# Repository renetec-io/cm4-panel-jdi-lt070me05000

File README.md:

Overview
======

This repository contains a PCB design and drivers for Raspberry Pi CM4 Сarrier with Hi-Res MIPI Display project.<br>
For details, see https://hackaday.io/project/176098-raspberry-pi-cm4-arrier-with-hi-res-mipi-display

The display used is JDI LT070ME05000 with Goodix touch input driver IC. The project also uses MCP23008 IO expander to save some GPIO pins.

Raspberry Pi only supports its official 7-inch MIPI DSI display with FKMS(Fake/Firmware KMS) out of the box. 
To make the display work, we need to use full KMS and Linux kernel driver for the panel.

Setup
======

1. Install the latest Raspberry PI OS image, either on SD card (with CM4 Lite) or onto eMMC.
   With Lite version, you can use [SD card instruction](https://www.raspberrypi.org/documentation/installation/installing-images), 
   otherwise use [eMMC instruction](https://www.raspberrypi.org/documentation/hardware/computemodule/cm-emmc-flashing.md).   
   The jumper that enables boot from usb is located near the micro-USB connector on the PCB.
   
1. Mount `boot` partition onto your computer.

1. Enable and connect the serial console.
   1. Add `enable_uart=1` to the config.txt file on `boot` partition.   
   1. Use the serial interface to connect to Raspberry Pi: [elinux.org instruction](https://elinux.org/RPi_Serial_Connection).   
   
1. Enable USB port. <br>
   By default, to conserve power, USB is not enabled on CM4.<br>
   To enable, add `dtoverlay=dwc2,dr_mode=host` to config.txt.
   
1. Boot your Raspberry Pi and connect it to the internet. If you have a module without Wi-Fi, 
   you need a USB Wi-Fi or Ethernet adapter. 
   If Wi-Fi doesn't work, and you are receiving the message like "Could not communicate with wpa_supplicant" from raspi-config 
   when trying to set up wireless network, you may need to add the following
   ```
   allow-hotplug wlan0
   iface wlan0 inet manual
   wpa-conf /etc/wpa_supplicant/wpa_supplicant.conf
   ```
   to /etc/network/interfaces and then reboot.

1. On the Raspberry Pi, 
   1. Install git and dkms: 
   ```
   sudo apt-get update
   sudo apt-get install git dkms
   ```
   2. Clone the repository and install the drivers
   ```
   git clone https://github.com/renetec-io/cm4-panel-jdi-lt070me05000.git
   cd cm4-panel-jdi-lt070me05000
   ./setup.sh
   ```

1. Enable display driver.<br>
   Add the following in the end of /boot/config.txt:
   ```
   dtparam=i2c_vc=on   
   lcd_ignore=1   
   dtoverlay=vc4-kms-v3d-pi4,noaudio   
   dtoverlay=cm4-dsi-lt070me05000   
   ```
   
1. Enable sound.<br>
   Add the following to /boot/config.txt:
   ```
   # Sound configuration   
   dtparam=audio=on   
   dtoverlay=hifiberry-dac   
   dtoverlay=i2s-mmap   
   ```   

8. Reboot.

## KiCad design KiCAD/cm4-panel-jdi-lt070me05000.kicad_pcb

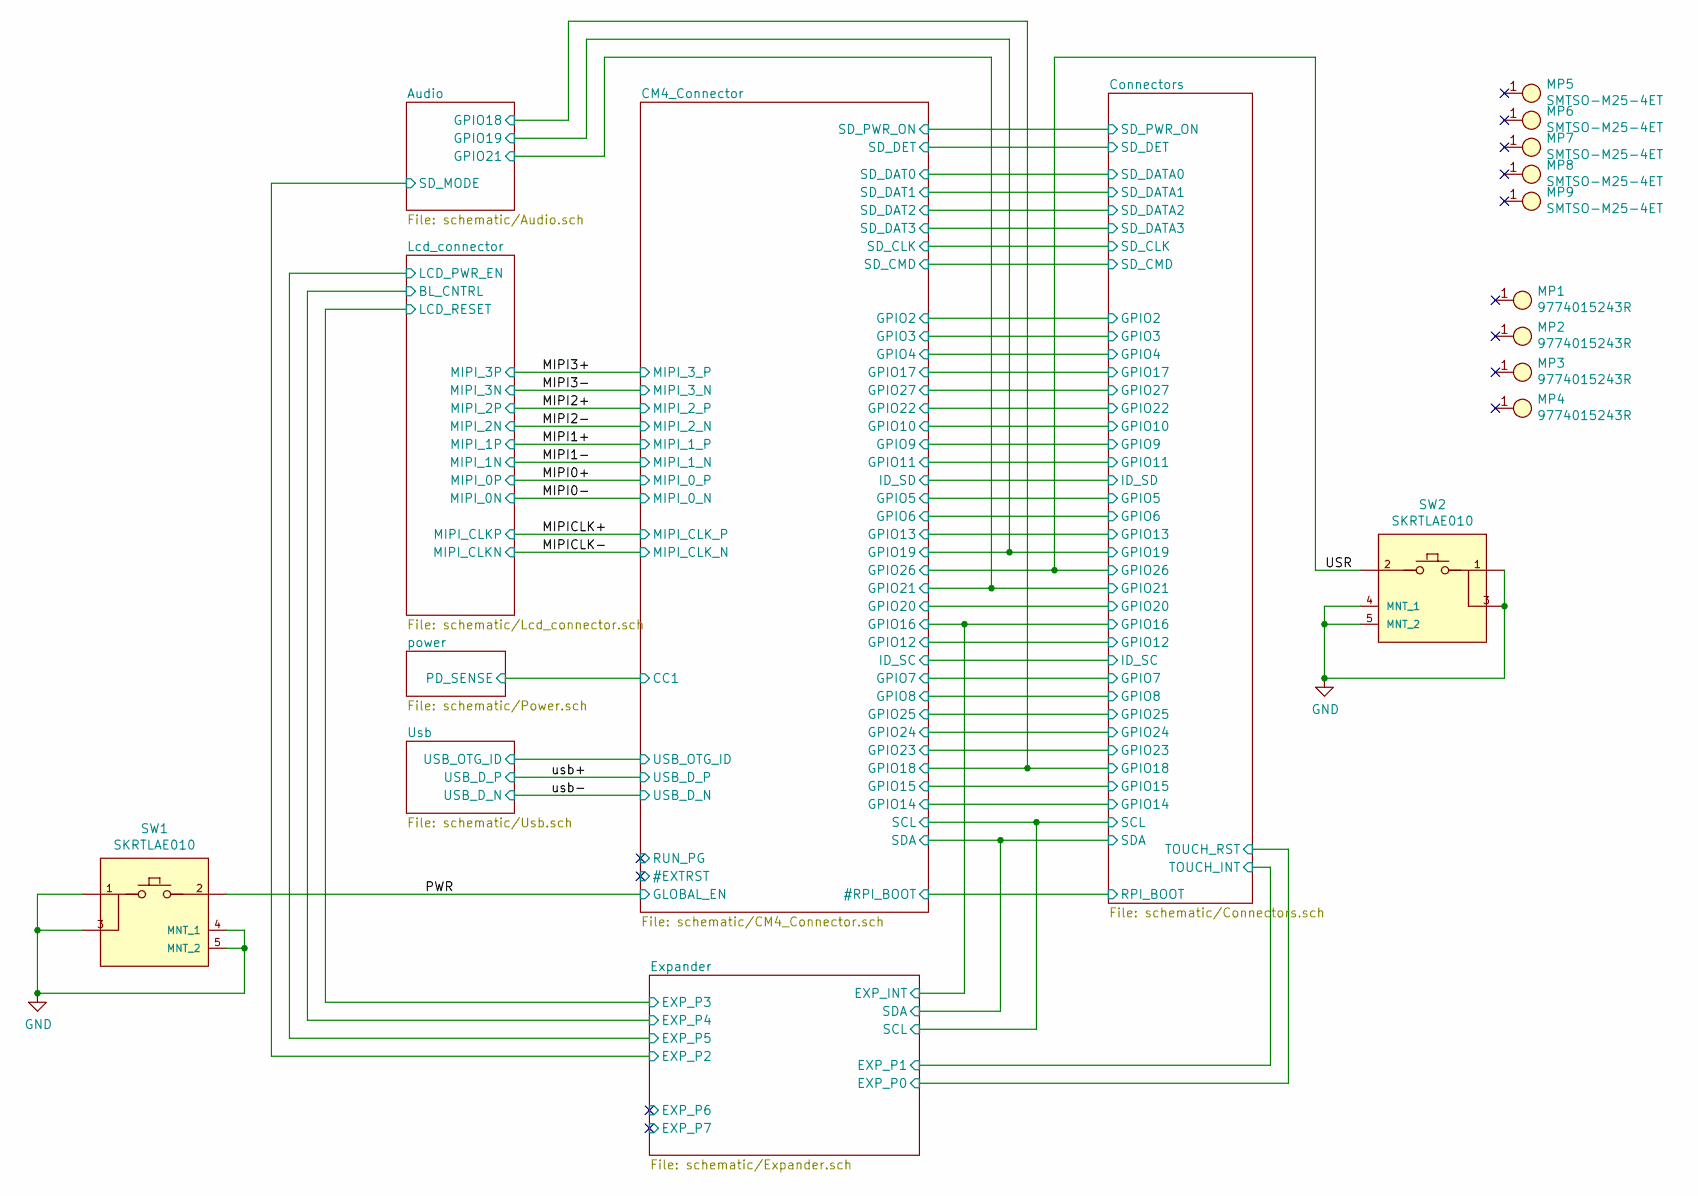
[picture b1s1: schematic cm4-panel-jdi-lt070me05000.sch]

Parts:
MP1, MP2, MP3, MP4: 9774015243R
MP5, MP6, MP7, MP8, MP9: SMTSO-M25-4ET
SW1, SW2: SKRTLAE010; ALPS-SKRTLAE010-0-0-0; voltage rating DC 12V; mouser part number 688-SKRTLA; mouser description Switch Tactile N.O. SPST Round Button J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

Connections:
/PWR: SW1.2; also elsewhere on the board
/USR: SW2.2; also elsewhere on the board
GND: SW1.1, SW1.3, SW1.4 (MNT_1), SW1.5 (MNT_2), SW2.1, SW2.3, SW2.4 (MNT_1), SW2.5 (MNT_2); also elsewhere on the board

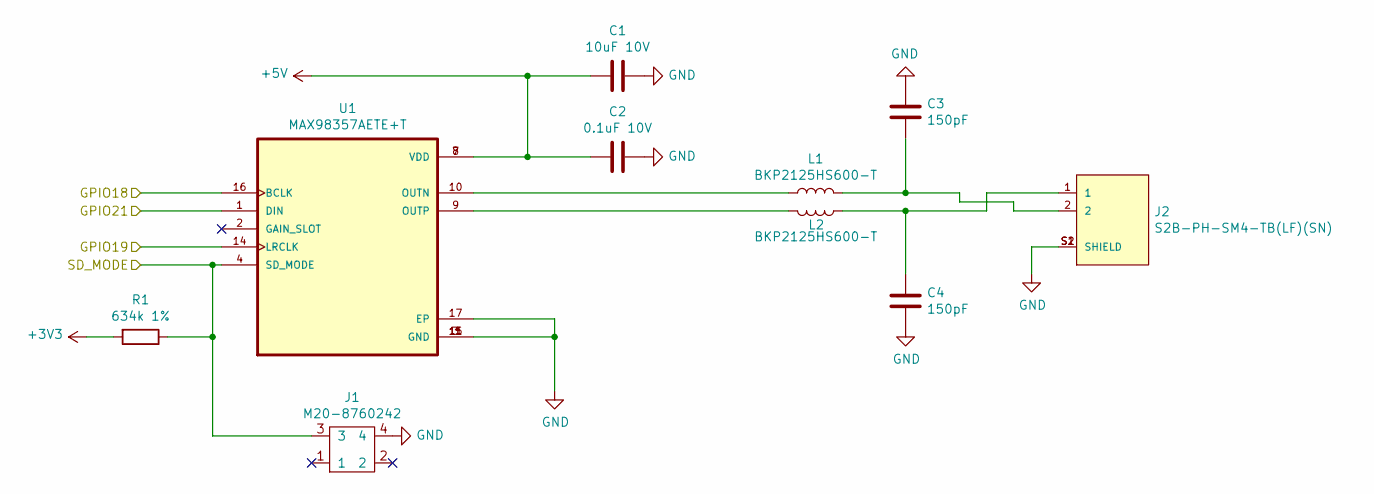
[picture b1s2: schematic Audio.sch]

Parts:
C1: 10uF 10V; C_0603_1608Metric
C2: 0.1uF 10V; C_0603_1608Metric
C3, C4: 150pF; C_0603_1608Metric
J1: M20-8760242
J2: S2B-PH-SM4-TB(LF)(SN); JST_S2B-PH-SM4-TB(LF)(SN)
L1, L2: BKP2125HS600-T; L_0805_2012Metric
R1: 634k 1%; R_0603_1608Metric
U1: MAX98357AETE+T; QFN50P300X300X80-17N

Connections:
+3V3: R1.2; also elsewhere on the board
+5V: C1.2, C2.2, U1.7 (VDD), U1.8 (VDD); also elsewhere on the board
/Audio/GPIO18: U1.16 (BCLK); also elsewhere on the board
/Audio/GPIO19: U1.14 (LRCLK); also elsewhere on the board
/Audio/GPIO21: U1.1 (DIN); also elsewhere on the board
/Expander/EXP_P2: J1.3, R1.1, U1.4 (SD_MODE); also elsewhere on the board
GND: C1.1, C2.1, C3.2, C4.1, J1.4, J2.S1 (SHIELD), J2.S2 (SHIELD), U1.3 (GND), U1.11 (GND), U1.15 (GND), U1.17 (EP); also elsewhere on the board
unnamed: C3.1, J2.2, L1.2
unnamed: C4.2, J2.1, L2.2
unnamed: L1.1, U1.10 (OUTN)
unnamed: L2.1, U1.9 (OUTP)

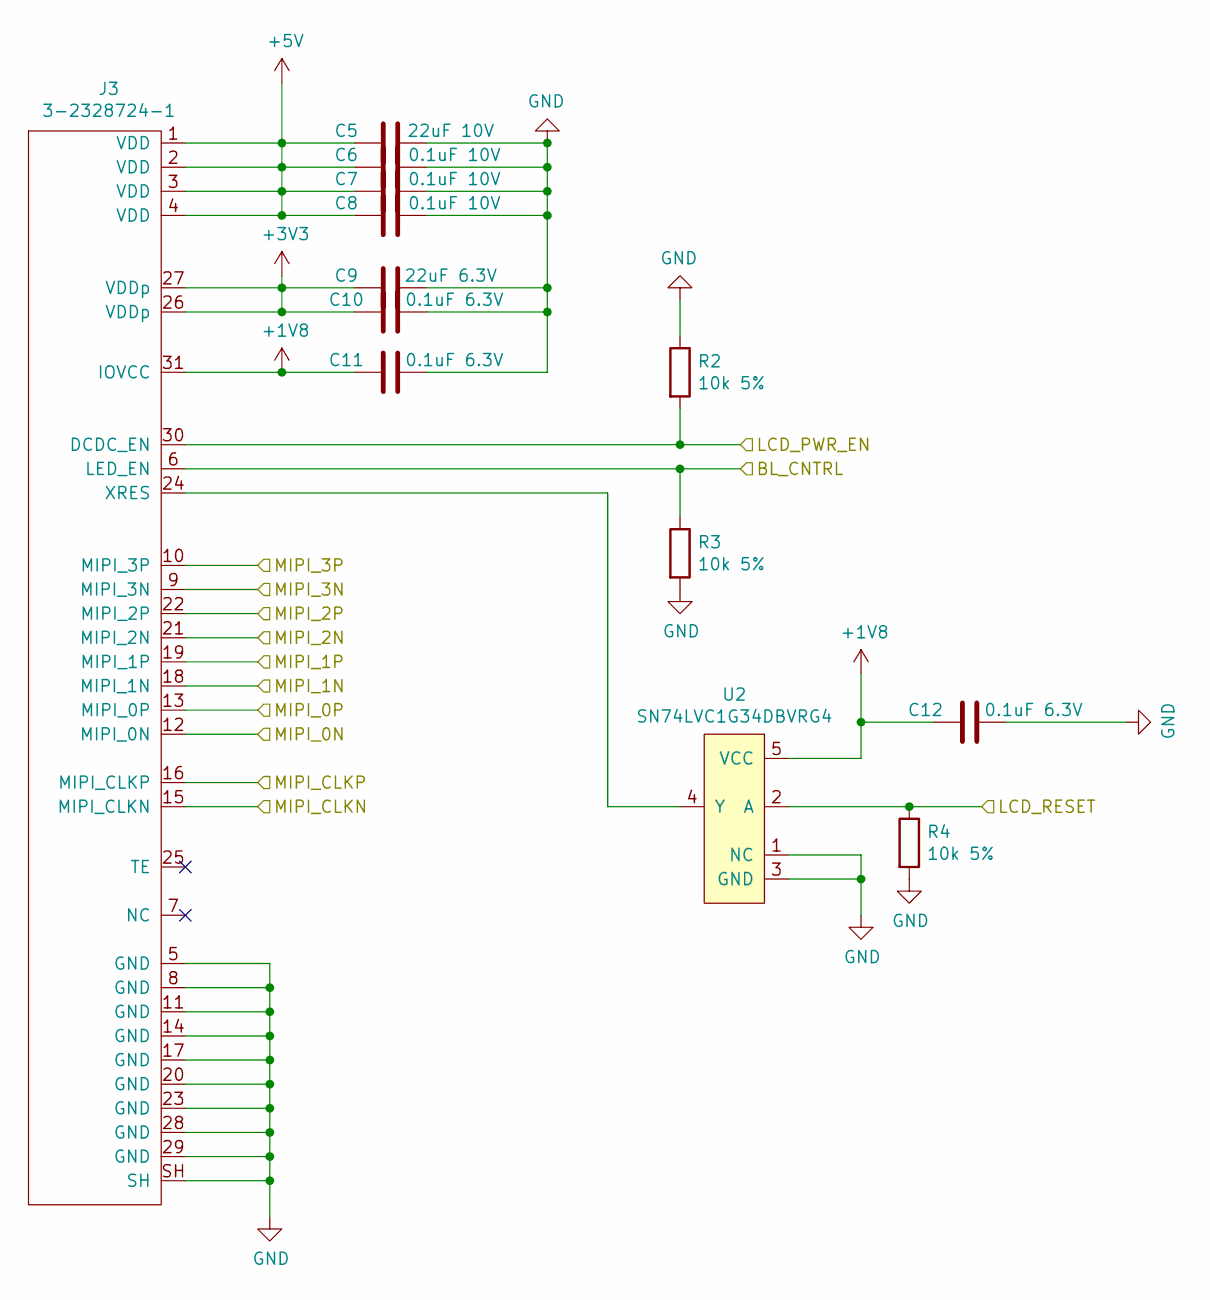
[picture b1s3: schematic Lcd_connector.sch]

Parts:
C5: 22uF 10V; C_0805_2012Metric
C6, C7, C8: 0.1uF 10V; C_0603_1608Metric
C9: 22uF 6.3V; C_0805_2012Metric
C10, C11, C12: 0.1uF 6.3V; C_0603_1608Metric
J3: 3-2328724-1
R2, R3, R4: 10k 5%; R_0603_1608Metric
U2: SN74LVC1G34DBVRG4; SOT95P280X145-5N

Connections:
+1V8: C11.2, C12.2, J3.31 (IOVCC), U2.5 (VCC); also elsewhere on the board
+3V3: C9.2, C10.2, J3.26 (VDDp), J3.27 (VDDp); also elsewhere on the board
+5V: C5.2, C6.2, C7.2, C8.2, J3.1 (VDD), J3.2 (VDD), J3.3 (VDD), J3.4 (VDD); also elsewhere on the board
/Expander/EXP_P3: R4.1, U2.2 (A); also elsewhere on the board
/Expander/EXP_P5: J3.30 (DCDC_EN), R2.2; also elsewhere on the board
/Lcd_connector/BL_CNTRL: J3.6 (LED_EN), R3.1; also elsewhere on the board
/MIPI0+: J3.13 (MIPI_0P); also elsewhere on the board
/MIPI0-: J3.12 (MIPI_0N); also elsewhere on the board
/MIPI1+: J3.19 (MIPI_1P); also elsewhere on the board
/MIPI1-: J3.18 (MIPI_1N); also elsewhere on the board
/MIPI2+: J3.22 (MIPI_2P); also elsewhere on the board
/MIPI2-: J3.21 (MIPI_2N); also elsewhere on the board
/MIPI3+: J3.10 (MIPI_3P); also elsewhere on the board
/MIPI3-: J3.9 (MIPI_3N); also elsewhere on the board
/MIPICLK+: J3.16 (MIPI_CLKP); also elsewhere on the board
/MIPICLK-: J3.15 (MIPI_CLKN); also elsewhere on the board
GND: C5.1, C6.1, C7.1, C8.1, C9.1, C10.1, C11.1, C12.1, J3.5 (GND), J3.8 (GND), J3.11 (GND), J3.14 (GND), J3.17 (GND), J3.20 (GND), J3.23 (GND), J3.28 (GND), J3.29 (GND), J3.SH, R2.1, R3.2, R4.2, U2.1 (NC), U2.3 (GND); also elsewhere on the board
unnamed: J3.24 (XRES), U2.4 (Y)

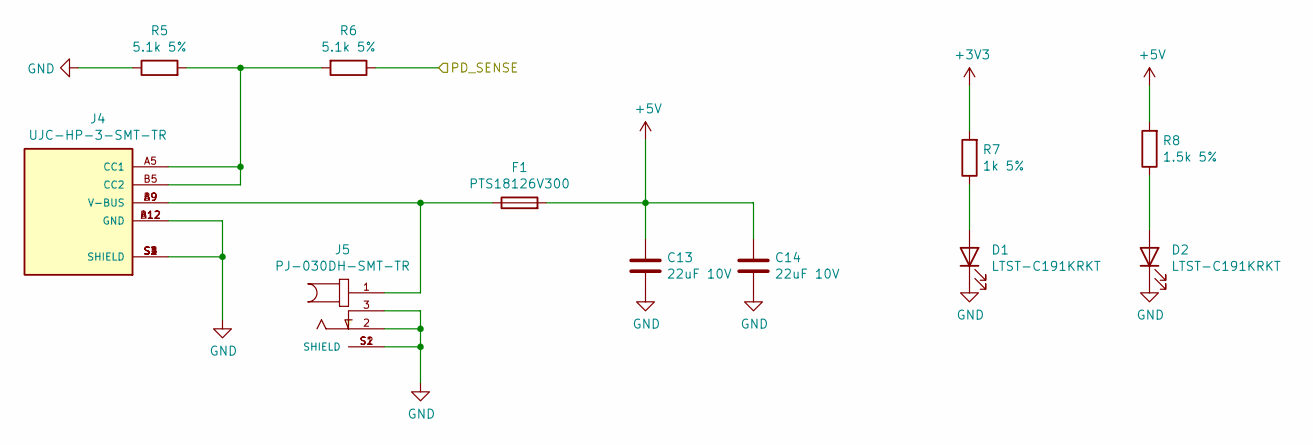
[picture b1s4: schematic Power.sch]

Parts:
C13, C14: 22uF 10V; C_0805_2012Metric
D1, D2: LTST-C191KRKT; LED_0603_1608Metric
F1: PTS18126V300; Fuse_1812_4532Metric
J4: UJC-HP-3-SMT-TR; CUI_UJC-HP-3-SMT-TR; PARTREV 1.0
J5: PJ-030DH-SMT-TR; CUI_PJ-030DH-SMT-TR; PARTREV 1.03
R5, R6: 5.1k 5%; R_0603_1608Metric
R7: 1k 5%; R_0603_1608Metric
R8: 1.5k 5%; R_0603_1608Metric

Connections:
+3V3: R7.2; also elsewhere on the board
+5V: C13.1, C14.1, F1.2, R8.2; also elsewhere on the board
/CM4_Connector/CC1: R6.1; also elsewhere on the board
GND: C13.2, C14.2, D1.1 (K), D2.1 (K), J4.A12 (GND), J4.B12 (GND), J4.S1 (SHIELD), J4.S2 (SHIELD), J4.S3 (SHIELD), J4.S4 (SHIELD), J5.2, J5.3, J5.S1 (SHIELD), J5.S2 (SHIELD), R5.1; also elsewhere on the board
unnamed: D1.2 (A), R7.1
unnamed: D2.2 (A), R8.1
unnamed: F1.1, J4.A9 (V-BUS), J4.B9 (V-BUS), J5.1
unnamed: J4.A5 (CC1), J4.B5 (CC2), R5.2, R6.2

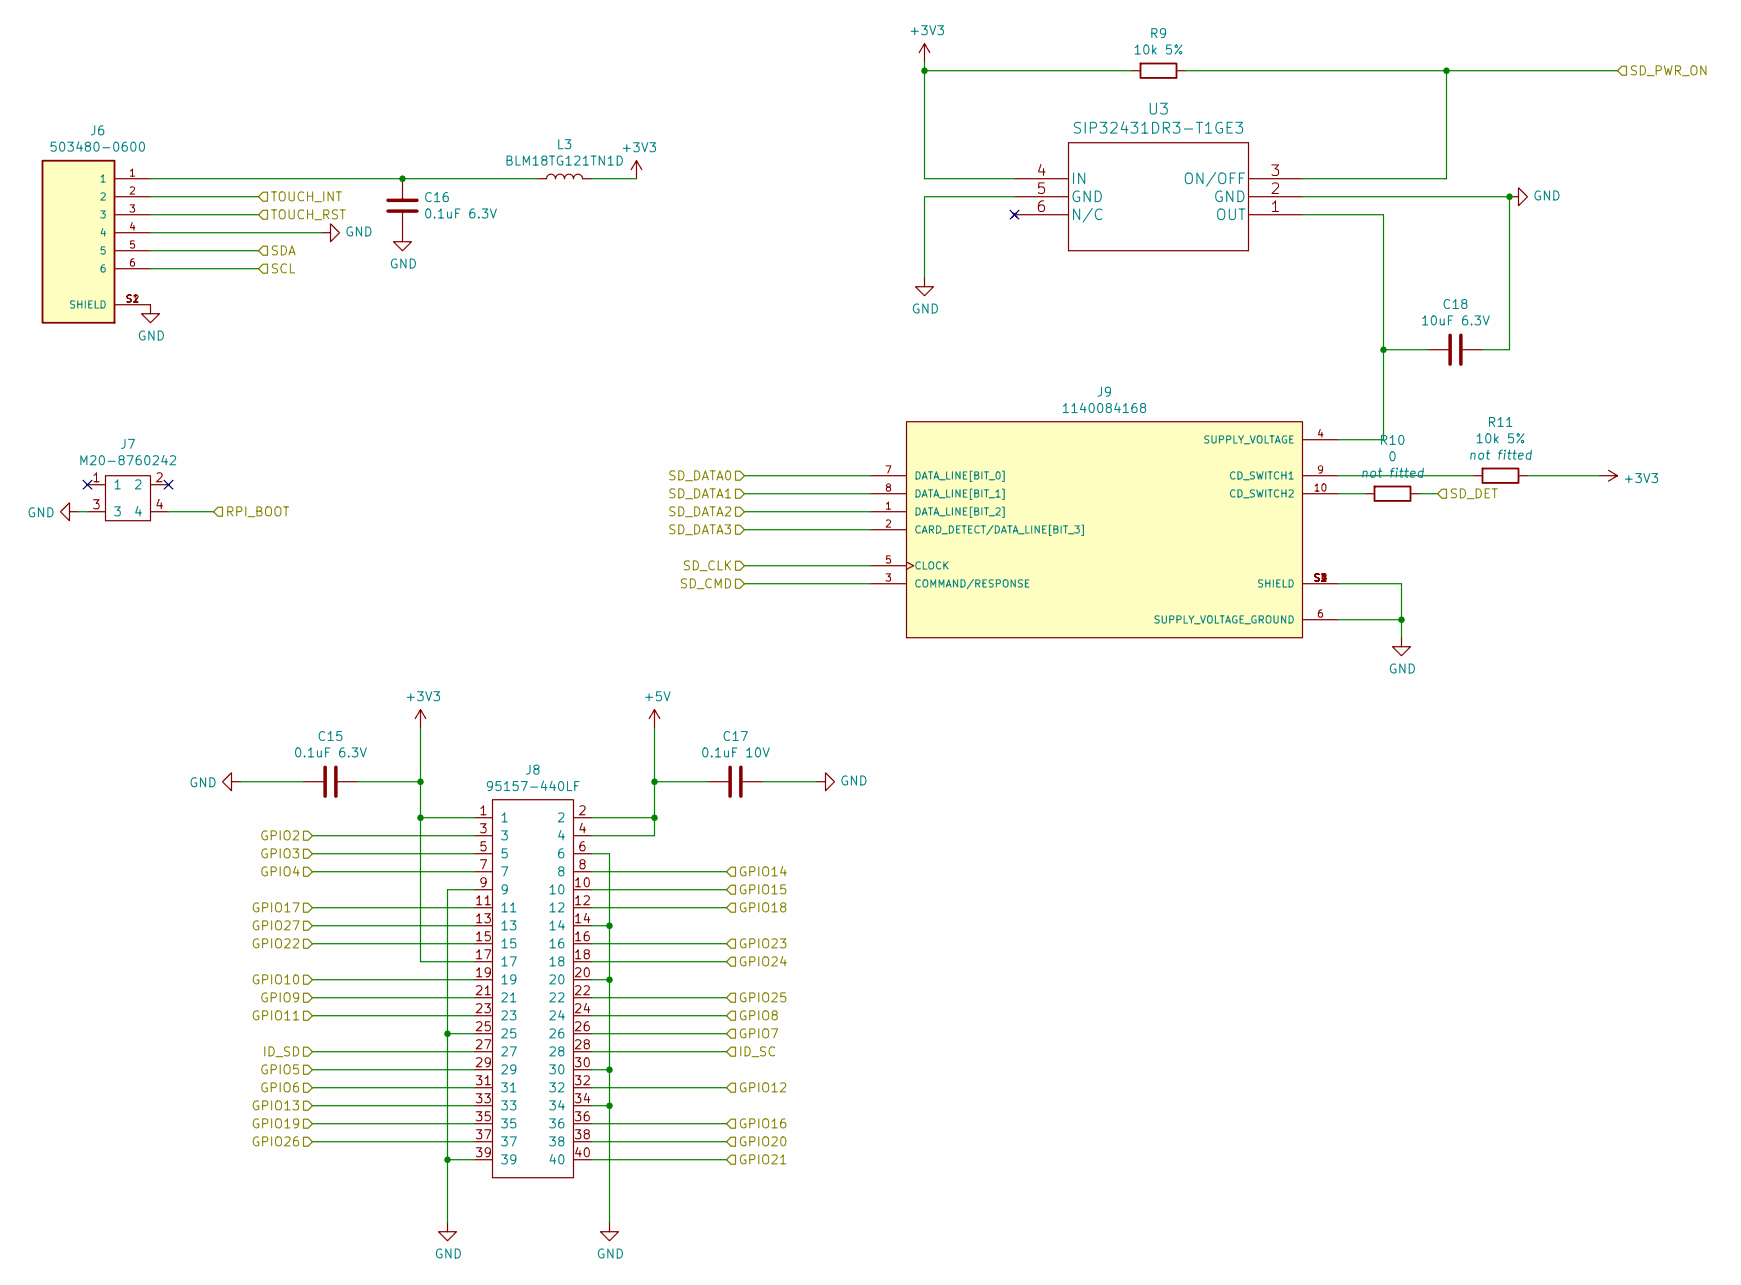
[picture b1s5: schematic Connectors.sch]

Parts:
C15, C16: 0.1uF 6.3V; C_0603_1608Metric
C17: 0.1uF 10V; C_0603_1608Metric
C18: 10uF 6.3V; C_0603_1608Metric
J6: 503480-0600; MOLEX_503480-0600; PARTREV H
J7: M20-8760242
J8: 95157-440LF
J9: 1140084168; AMPHENOL_1140084168; PARTREV A
L3: BLM18TG121TN1D; L_0603_1608Metric
R9, R11: 10k 5%; R_0603_1608Metric
R10: 0; R_0603_1608Metric
U3: SIP32431DR3-T1GE3

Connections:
+3V3: C15.1, J8.1, J8.17, L3.2, R9.2, R11.1, U3.4 (IN); also elsewhere on the board
+5V: C17.2, J8.2, J8.4; also elsewhere on the board
/Audio/GPIO18: J8.12; also elsewhere on the board
/Audio/GPIO19: J8.35; also elsewhere on the board
/Audio/GPIO21: J8.40; also elsewhere on the board
/CM4_Connector/#RPI_BOOT: J7.4; also elsewhere on the board
/CM4_Connector/GPIO2: J8.3; also elsewhere on the board
/CM4_Connector/GPIO3: J8.5; also elsewhere on the board
/CM4_Connector/GPIO4: J8.7; also elsewhere on the board
/CM4_Connector/GPIO5: J8.29; also elsewhere on the board
/CM4_Connector/GPIO6: J8.31; also elsewhere on the board
/CM4_Connector/GPIO7: J8.26; also elsewhere on the board
/CM4_Connector/GPIO8: J8.24; also elsewhere on the board
/CM4_Connector/GPIO9: J8.21; also elsewhere on the board
/CM4_Connector/GPIO10: J8.19; also elsewhere on the board
/CM4_Connector/GPIO11: J8.23; also elsewhere on the board
/CM4_Connector/GPIO12: J8.32; also elsewhere on the board
/CM4_Connector/GPIO13: J8.33; also elsewhere on the board
/CM4_Connector/GPIO14: J8.8; also elsewhere on the board
/CM4_Connector/GPIO15: J8.10; also elsewhere on the board
/CM4_Connector/GPIO17: J8.11; also elsewhere on the board
/CM4_Connector/GPIO20: J8.38; also elsewhere on the board
/CM4_Connector/GPIO22: J8.15; also elsewhere on the board
/CM4_Connector/GPIO23: J8.16; also elsewhere on the board
/CM4_Connector/GPIO24: J8.18; also elsewhere on the board
/CM4_Connector/GPIO25: J8.22; also elsewhere on the board
/CM4_Connector/GPIO27: J8.13; also elsewhere on the board
/CM4_Connector/ID_SC: J8.28; also elsewhere on the board
/CM4_Connector/ID_SD: J8.27; also elsewhere on the board
/CM4_Connector/SCL: J6.6; also elsewhere on the board
/CM4_Connector/SDA: J6.5; also elsewhere on the board
/CM4_Connector/SD_CLK: J9.5 (CLOCK); also elsewhere on the board
/CM4_Connector/SD_CMD: J9.3 (COMMAND/RESPONSE); also elsewhere on the board
/CM4_Connector/SD_DAT0: J9.7 (DATA_LINE[BIT_0]); also elsewhere on the board
/CM4_Connector/SD_DAT1: J9.8 (DATA_LINE[BIT_1]); also elsewhere on the board
/CM4_Connector/SD_DAT2: J9.1 (DATA_LINE[BIT_2]); also elsewhere on the board
/CM4_Connector/SD_DAT3: J9.2 (CARD_DETECT/DATA_LINE[BIT_3]); also elsewhere on the board
/CM4_Connector/SD_DET: R10.1; also elsewhere on the board
/CM4_Connector/SD_PWR_ON: R9.1, U3.3 (ON/OFF); also elsewhere on the board
/Expander/EXP_INT: J8.36; also elsewhere on the board
/Expander/EXP_P0: J6.3; also elsewhere on the board
/Expander/EXP_P1: J6.2; also elsewhere on the board
/USR: J8.37; also elsewhere on the board
GND: C15.2, C16.1, C17.1, C18.1, J6.4, J6.S1 (SHIELD), J6.S2 (SHIELD), J7.3, J8.6, J8.9, J8.14, J8.20, J8.25, J8.30, J8.34, J8.39, J9.6 (SUPPLY_VOLTAGE_GROUND), J9.S1 (SHIELD), J9.S2 (SHIELD), J9.S3 (SHIELD), J9.S4 (SHIELD), U3.2 (GND), U3.5 (GND); also elsewhere on the board
unnamed: C16.2, J6.1, L3.1
unnamed: C18.2, J9.4 (SUPPLY_VOLTAGE), U3.1 (OUT)
unnamed: J9.9 (CD_SWITCH1), R11.2
unnamed: J9.10 (CD_SWITCH2), R10.2

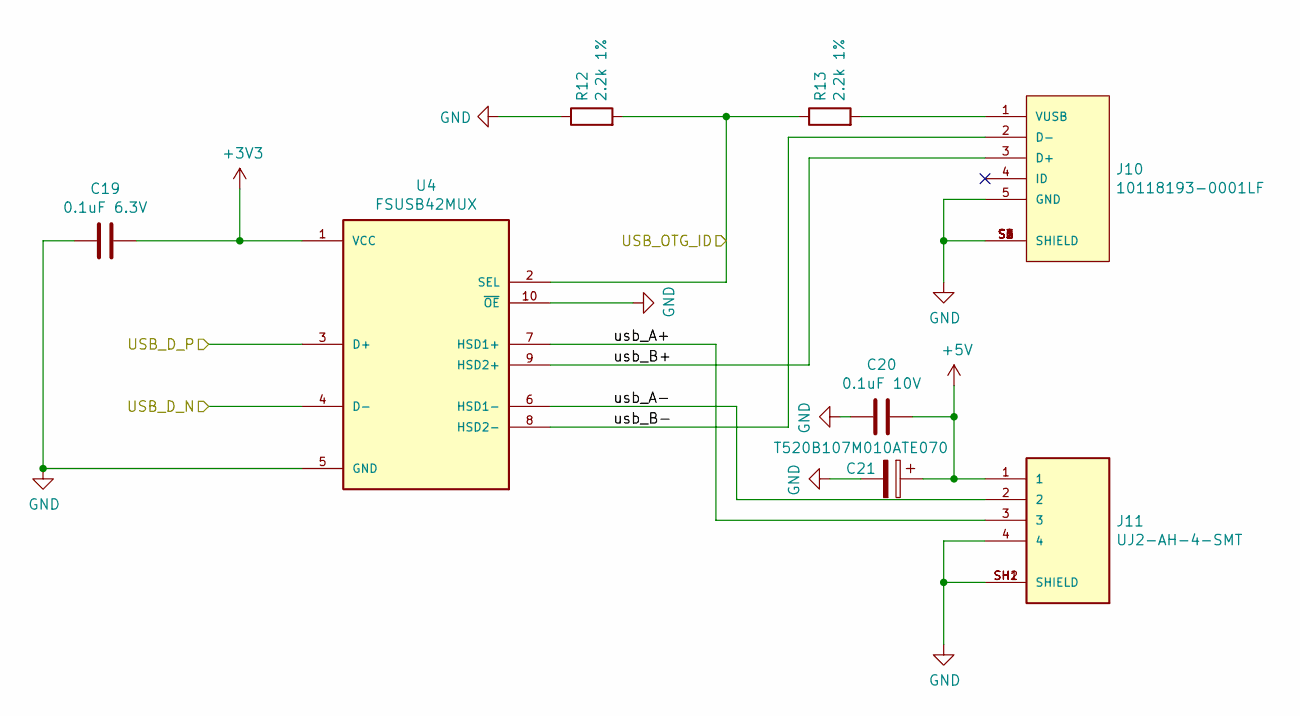
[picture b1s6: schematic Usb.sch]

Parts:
C19: 0.1uF 6.3V; C_0603_1608Metric
C20: 0.1uF 10V; C_0603_1608Metric
C21: T520B107M010ATE070; T520B227M006ATE045
J10: 10118193-0001LF; FCI_10118193-0001LF
J11: UJ2-AH-4-SMT; CUI_UJ2-AH-4-SMT; PART_REV 1.01
R12, R13: 2.2k 1%; R_0603_1608Metric
U4: FSUSB42MUX; SOP50P490X110-10N; PARTREV 1.25

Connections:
+3V3: C19.1, U4.1 (VCC); also elsewhere on the board
+5V: C20.1, C21.1, J11.1; also elsewhere on the board
/CM4_Connector/USB_OTG_ID: R12.2, R13.1, U4.2 (SEL); also elsewhere on the board
/Usb/usb_A+: J11.3, U4.7 (HSD1+)
/Usb/usb_A-: J11.2, U4.6 (HSD1-)
/Usb/usb_B+: J10.3 (D+), U4.9 (HSD2+)
/Usb/usb_B-: J10.2 (D-), U4.8 (HSD2-)
/usb+: U4.3 (D+); also elsewhere on the board
/usb-: U4.4 (D-); also elsewhere on the board
GND: C19.2, C20.2, C21.2, J10.5 (GND), J10.S1 (SHIELD), J10.S2 (SHIELD), J10.S3 (SHIELD), J10.S4 (SHIELD), J10.S5 (SHIELD), J10.S6 (SHIELD), J11.4, J11.SH1 (SHIELD), J11.SH2 (SHIELD), R12.1, U4.5 (GND), U4.10 (~OE); also elsewhere on the board
unnamed: J10.1 (VUSB), R13.2

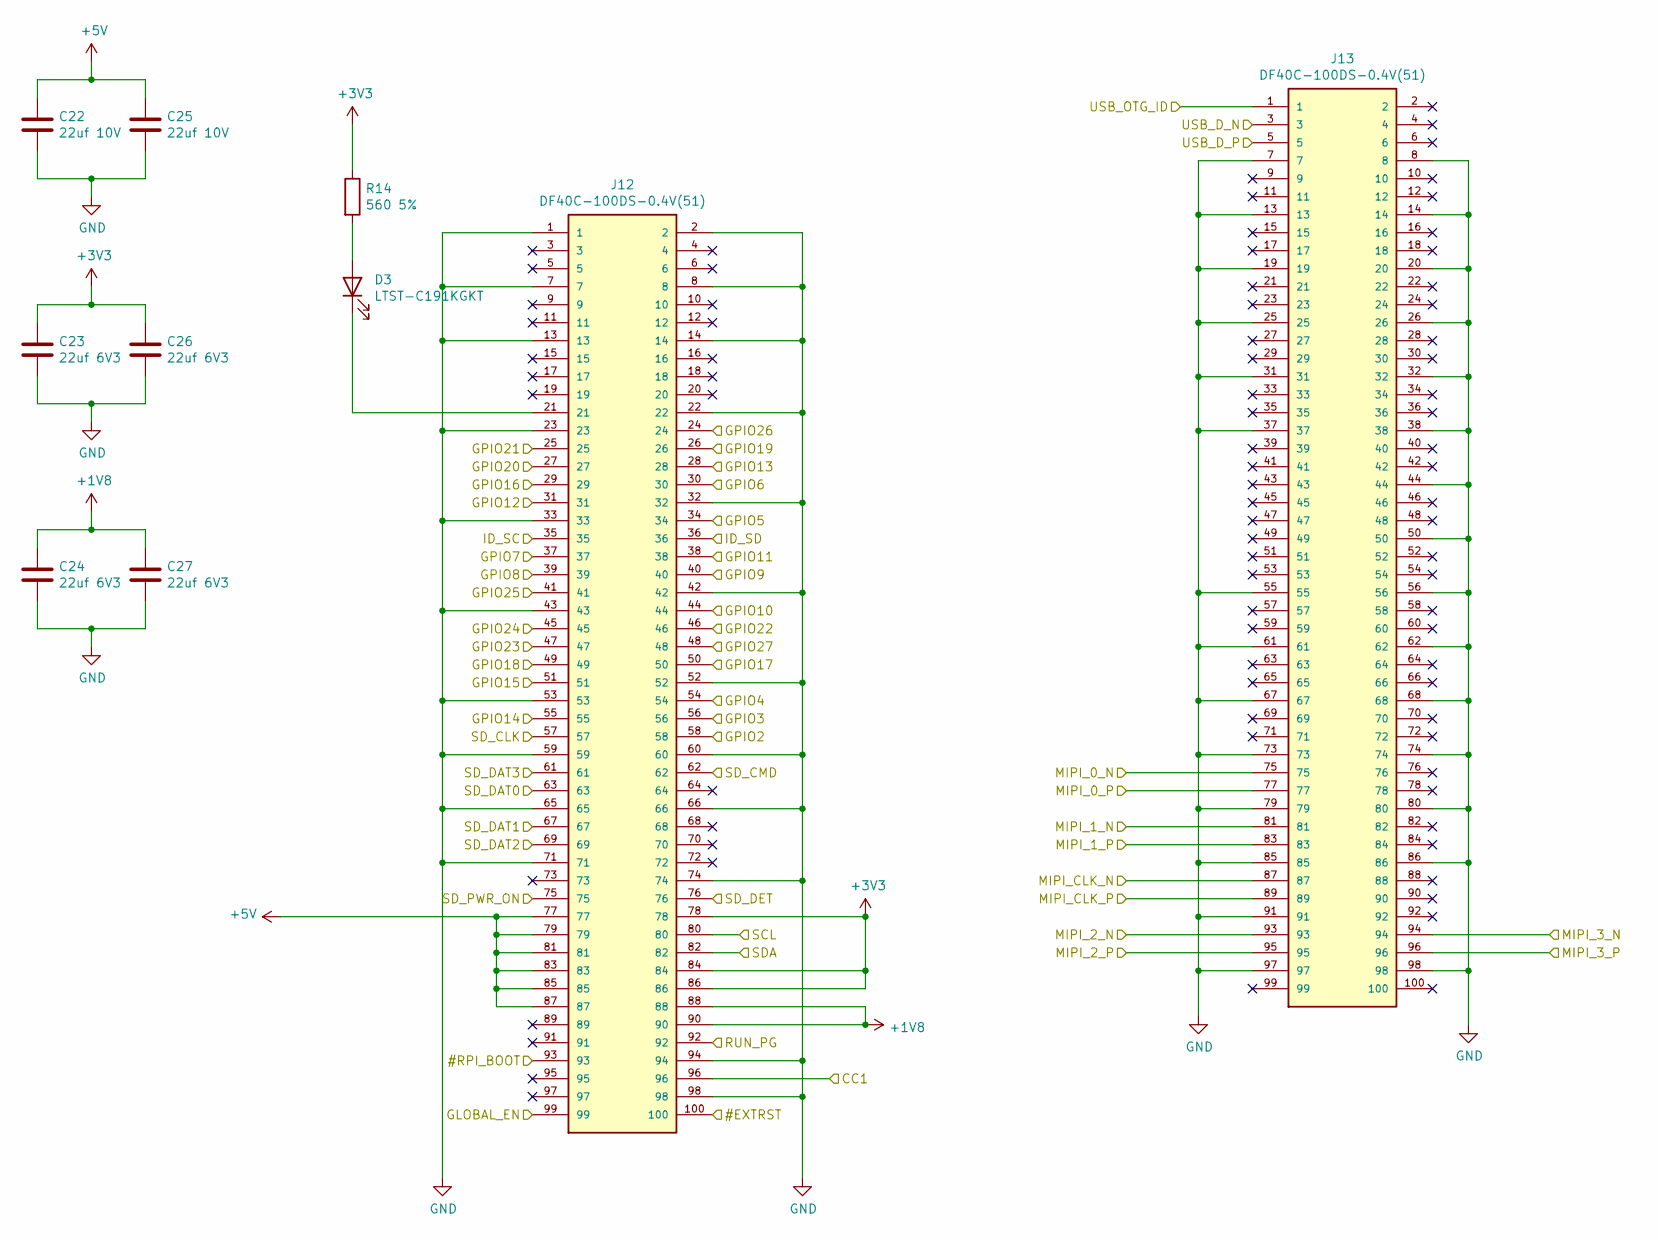
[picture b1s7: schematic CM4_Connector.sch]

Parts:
C22, C25: 22uf 10V; C_0805_2012Metric
C23, C24, C26, C27: 22uf 6V3; C_0805_2012Metric
D3: LTST-C191KGKT; LED_0603_1608Metric
J12, J13: DF40C-100DS-0.4V(51); HRS_DF40C-100DS-0.4V(51)
R14: 560 5%; R_0603_1608Metric

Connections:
+1V8: C24.1, C27.1, J12.88, J12.90; also elsewhere on the board
+3V3: C23.1, C26.1, J12.78, J12.84, J12.86, R14.1; also elsewhere on the board
+5V: C22.1, C25.1, J12.77, J12.79, J12.81, J12.83, J12.85, J12.87; also elsewhere on the board
/Audio/GPIO18: J12.49; also elsewhere on the board
/Audio/GPIO19: J12.26; also elsewhere on the board
/Audio/GPIO21: J12.25; also elsewhere on the board
/CM4_Connector/#EXTRST: J12.100
/CM4_Connector/#RPI_BOOT: J12.93; also elsewhere on the board
/CM4_Connector/CC1: J12.96; also elsewhere on the board
/CM4_Connector/GPIO2: J12.58; also elsewhere on the board
/CM4_Connector/GPIO3: J12.56; also elsewhere on the board
/CM4_Connector/GPIO4: J12.54; also elsewhere on the board
/CM4_Connector/GPIO5: J12.34; also elsewhere on the board
/CM4_Connector/GPIO6: J12.30; also elsewhere on the board
/CM4_Connector/GPIO7: J12.37; also elsewhere on the board
/CM4_Connector/GPIO8: J12.39; also elsewhere on the board
/CM4_Connector/GPIO9: J12.40; also elsewhere on the board
/CM4_Connector/GPIO10: J12.44; also elsewhere on the board
/CM4_Connector/GPIO11: J12.38; also elsewhere on the board
/CM4_Connector/GPIO12: J12.31; also elsewhere on the board
/CM4_Connector/GPIO13: J12.28; also elsewhere on the board
/CM4_Connector/GPIO14: J12.55; also elsewhere on the board
/CM4_Connector/GPIO15: J12.51; also elsewhere on the board
/CM4_Connector/GPIO17: J12.50; also elsewhere on the board
/CM4_Connector/GPIO20: J12.27; also elsewhere on the board
/CM4_Connector/GPIO22: J12.46; also elsewhere on the board
/CM4_Connector/GPIO23: J12.47; also elsewhere on the board
/CM4_Connector/GPIO24: J12.45; also elsewhere on the board
/CM4_Connector/GPIO25: J12.41; also elsewhere on the board
/CM4_Connector/GPIO27: J12.48; also elsewhere on the board
/CM4_Connector/ID_SC: J12.35; also elsewhere on the board
/CM4_Connector/ID_SD: J12.36; also elsewhere on the board
/CM4_Connector/RUN_PG: J12.92
/CM4_Connector/SCL: J12.80; also elsewhere on the board
/CM4_Connector/SDA: J12.82; also elsewhere on the board
/CM4_Connector/SD_CLK: J12.57; also elsewhere on the board
/CM4_Connector/SD_CMD: J12.62; also elsewhere on the board
/CM4_Connector/SD_DAT0: J12.63; also elsewhere on the board
/CM4_Connector/SD_DAT1: J12.67; also elsewhere on the board
/CM4_Connector/SD_DAT2: J12.69; also elsewhere on the board
/CM4_Connector/SD_DAT3: J12.61; also elsewhere on the board
/CM4_Connector/SD_DET: J12.76; also elsewhere on the board
/CM4_Connector/SD_PWR_ON: J12.75; also elsewhere on the board
/CM4_Connector/USB_OTG_ID: J13.1; also elsewhere on the board
/Expander/EXP_INT: J12.29; also elsewhere on the board
/MIPI0+: J13.77; also elsewhere on the board
/MIPI0-: J13.75; also elsewhere on the board
/MIPI1+: J13.83; also elsewhere on the board
/MIPI1-: J13.81; also elsewhere on the board
/MIPI2+: J13.95; also elsewhere on the board
/MIPI2-: J13.93; also elsewhere on the board
/MIPI3+: J13.96; also elsewhere on the board
/MIPI3-: J13.94; also elsewhere on the board
/MIPICLK+: J13.89; also elsewhere on the board
/MIPICLK-: J13.87; also elsewhere on the board
/PWR: J12.99; also elsewhere on the board
/USR: J12.24; also elsewhere on the board
/usb+: J13.5; also elsewhere on the board
/usb-: J13.3; also elsewhere on the board
GND: C22.2, C23.2, C24.2, C25.2, C26.2, C27.2, J12.1, J12.2, J12.7, J12.8, J12.13, J12.14, J12.22, J12.23, J12.32, J12.33, J12.42, J12.43, J12.52, J12.53, J12.59, J12.60, J12.65, J12.66, J12.71, J12.74, J12.94, J12.98, J13.7, J13.8, J13.13, J13.14, J13.19, J13.20, J13.25, J13.26, J13.31, J13.32, J13.37, J13.38, J13.44, J13.50, J13.55, J13.56, J13.61, J13.62, J13.67, J13.68, J13.73, J13.74, J13.79, J13.80, J13.85, J13.86, J13.91, J13.97, J13.98; also elsewhere on the board
unnamed: D3.1 (K), J12.21
unnamed: D3.2 (A), R14.2

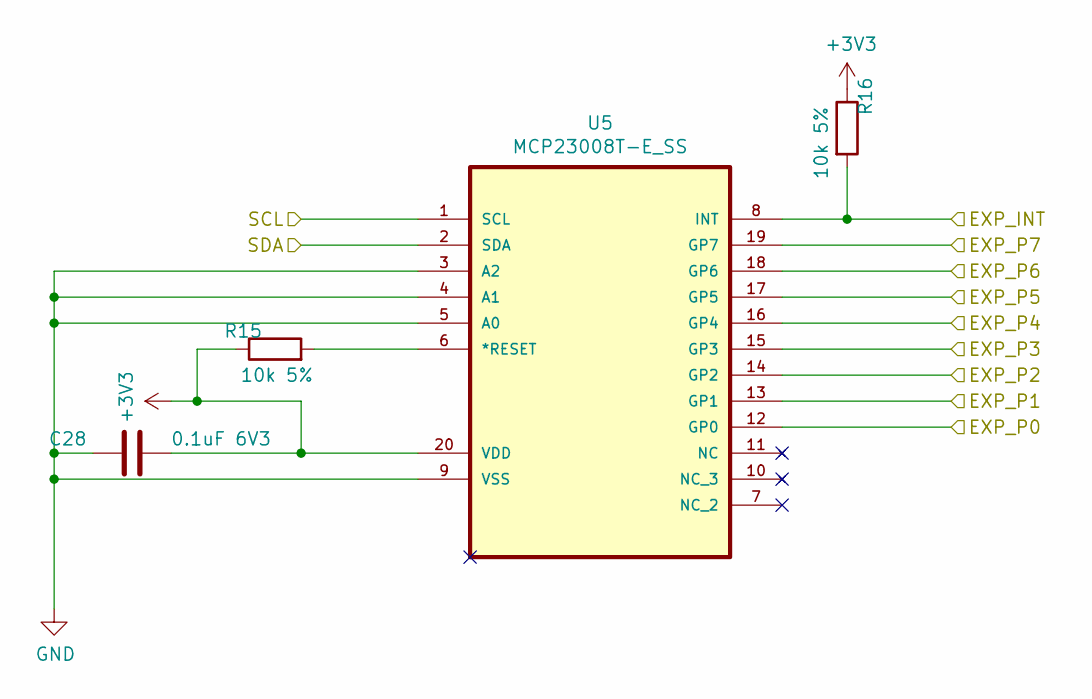
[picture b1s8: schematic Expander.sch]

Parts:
C28: 0.1uF 6V3; C_0603_1608Metric
R15, R16: 10k 5%; R_0603_1608Metric
U5: MCP23008T-E_SS; SOP65P780X200-20N; MPN MCP23008T-E/SS

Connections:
+3V3: C28.2, R15.1, R16.1, U5.20 (VDD); also elsewhere on the board
/CM4_Connector/SCL: U5.1 (SCL); also elsewhere on the board
/CM4_Connector/SDA: U5.2 (SDA); also elsewhere on the board
/Expander/EXP_INT: R16.2, U5.8 (INT); also elsewhere on the board
/Expander/EXP_P0: U5.12 (GP0); also elsewhere on the board
/Expander/EXP_P1: U5.13 (GP1); also elsewhere on the board
/Expander/EXP_P2: U5.14 (GP2); also elsewhere on the board
/Expander/EXP_P3: U5.15 (GP3); also elsewhere on the board
/Expander/EXP_P5: U5.17 (GP5); also elsewhere on the board
/Expander/EXP_P6: U5.18 (GP6)
/Expander/EXP_P7: U5.19 (GP7)
/Lcd_connector/BL_CNTRL: U5.16 (GP4); also elsewhere on the board
GND: C28.1, U5.3 (A2), U5.4 (A1), U5.5 (A0), U5.9 (VSS); also elsewhere on the board
unnamed: R15.2, U5.6 (*RESET)

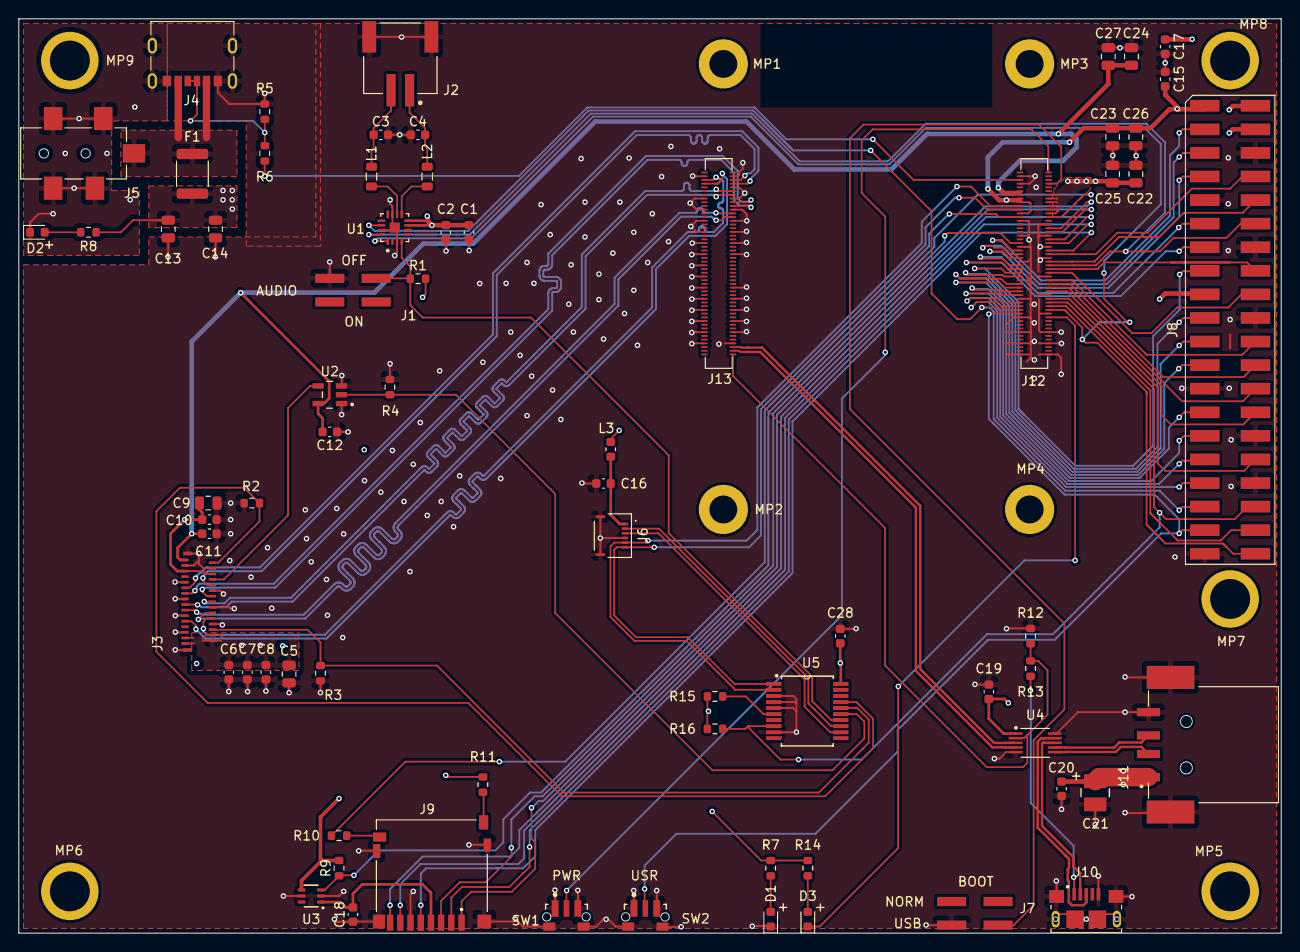
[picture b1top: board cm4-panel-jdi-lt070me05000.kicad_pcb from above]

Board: 4 copper layers, 136.0 x 98.5 mm, 80 parts (0 on the bottom side), 85 nets.

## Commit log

2021-07-26 Add PCB design
2021-07-26 Initial commit of the JDI LT070ME05000 driver

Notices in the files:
parts and their libraries:
Copyright 2016 Accelerated Designs. All rights reserved.
